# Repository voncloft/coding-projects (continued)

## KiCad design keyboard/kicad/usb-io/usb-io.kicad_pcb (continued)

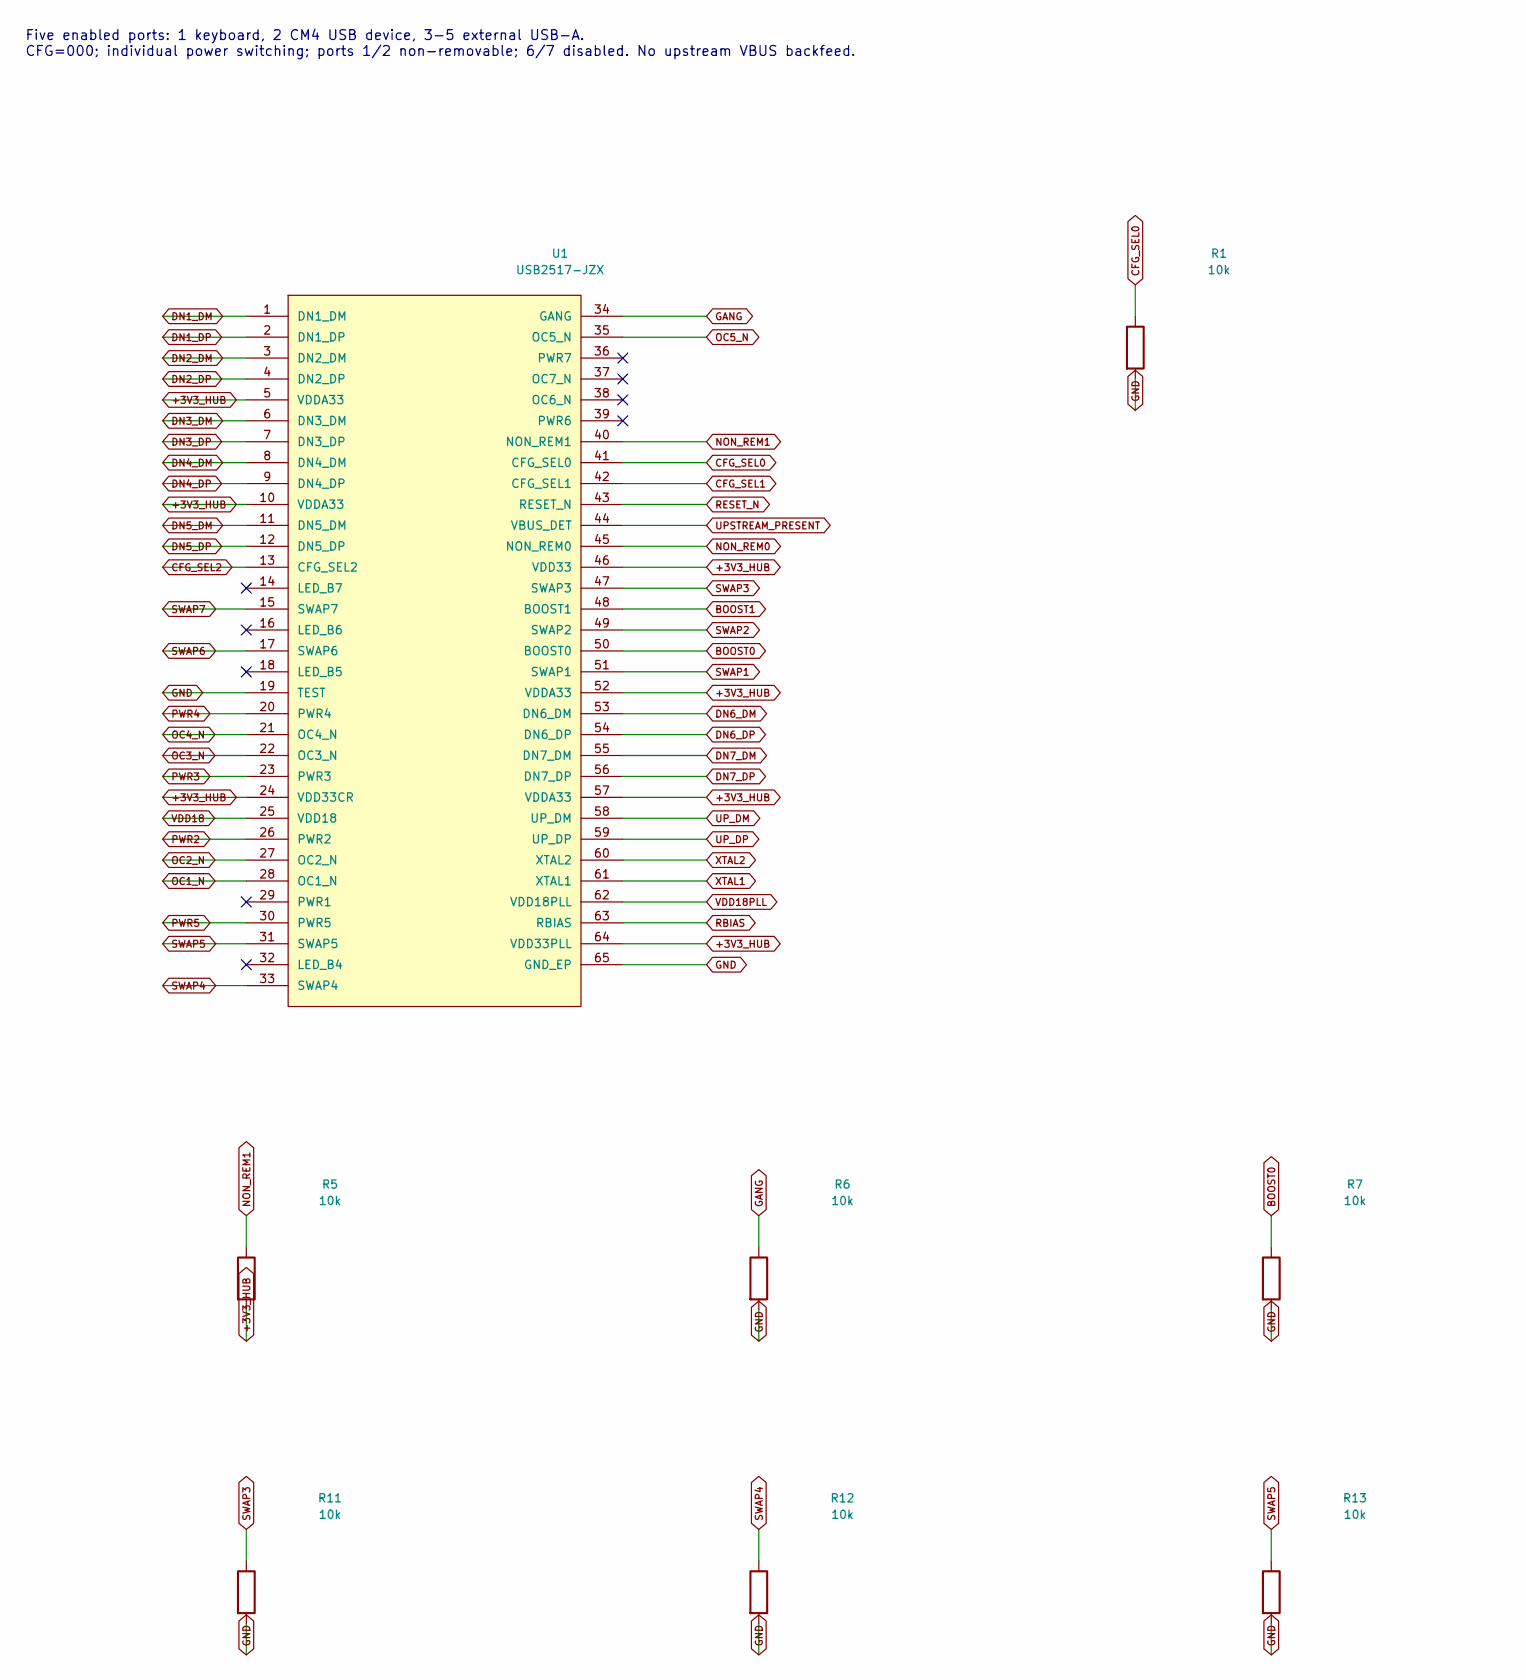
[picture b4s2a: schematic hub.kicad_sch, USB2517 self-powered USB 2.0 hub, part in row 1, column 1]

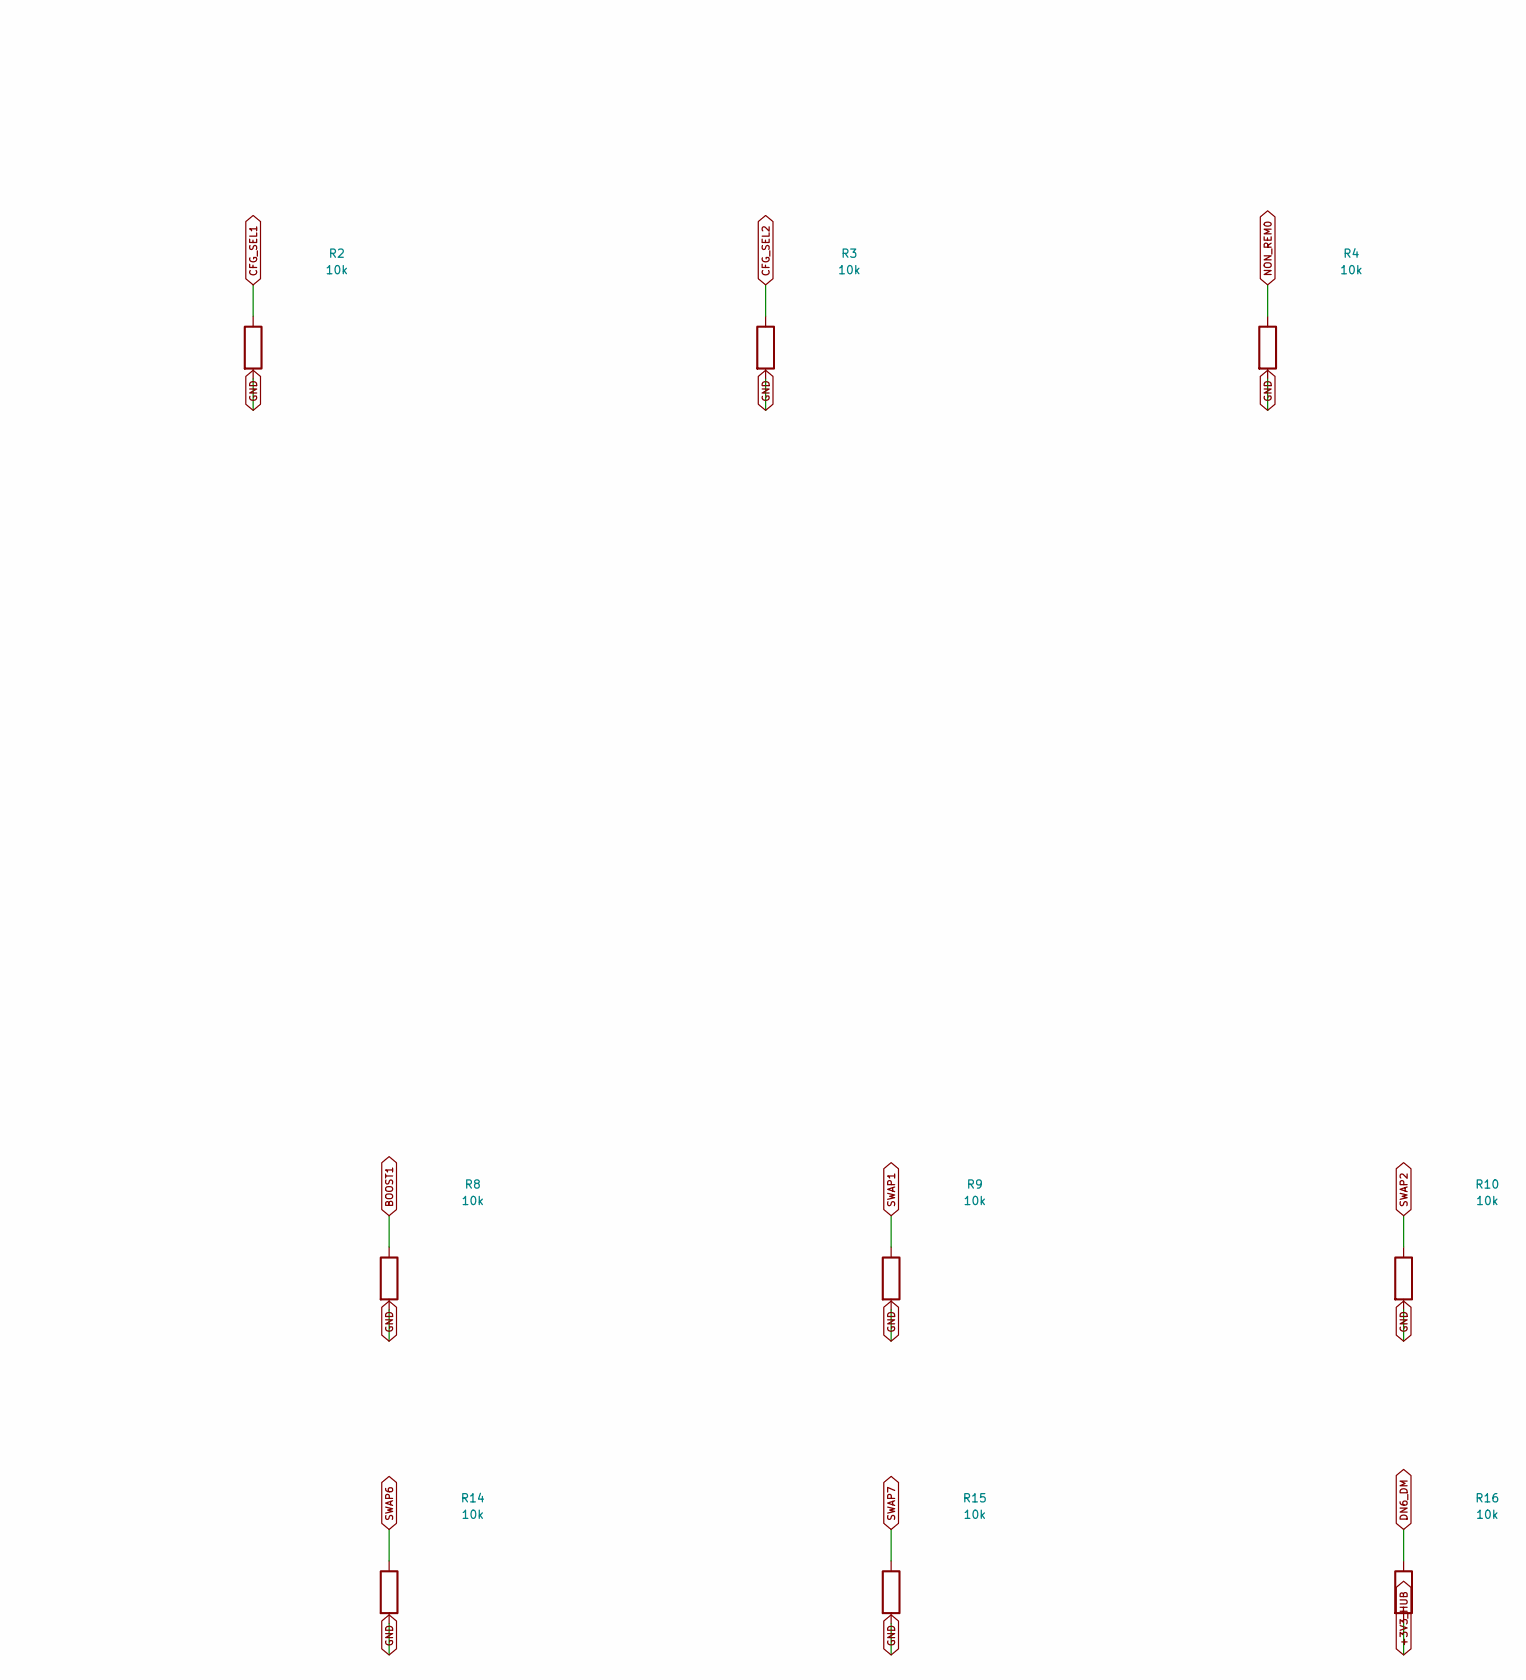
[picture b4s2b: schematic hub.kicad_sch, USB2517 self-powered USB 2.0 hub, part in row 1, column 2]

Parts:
R1, R2, R3, R4, R5, R6, R7, R8, R9, R10, R11, R12, R13, R14, R15, R16: 10k; R_0603_1608Metric
U1: USB2517-JZX; QFN-64-1EP_9x9mm_P0.5mm_EP4.7x4.7mm; MPN USB2517-JZX; JLCPCB C1521556

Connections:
+3V3_HUB: R5.2, R16.2, U1.5 (VDDA33), U1.10 (VDDA33), U1.24 (VDD33CR), U1.46 (VDD33), U1.52 (VDDA33), U1.57 (VDDA33), U1.64 (VDD33PLL); also elsewhere on the board
BOOST0: R7.1, U1.50 (BOOST0)
BOOST1: R8.1, U1.48 (BOOST1)
CFG_SEL0: R1.1, U1.41 (CFG_SEL0)
CFG_SEL1: R2.1, U1.42 (CFG_SEL1)
CFG_SEL2: R3.1, U1.13 (CFG_SEL2)
DN1_DM: U1.1 (DN1_DM); also elsewhere on the board
DN1_DP: U1.2 (DN1_DP); also elsewhere on the board
DN2_DM: U1.3 (DN2_DM); also elsewhere on the board
DN2_DP: U1.4 (DN2_DP); also elsewhere on the board
DN3_DM: U1.6 (DN3_DM); also elsewhere on the board
DN3_DP: U1.7 (DN3_DP); also elsewhere on the board
DN4_DM: U1.8 (DN4_DM); also elsewhere on the board
DN4_DP: U1.9 (DN4_DP); also elsewhere on the board
DN5_DM: U1.11 (DN5_DM); also elsewhere on the board
DN5_DP: U1.12 (DN5_DP); also elsewhere on the board
DN6_DM: R16.1, U1.53 (DN6_DM)
DN6_DP: U1.54 (DN6_DP); also elsewhere on the board
DN7_DM: U1.55 (DN7_DM); also elsewhere on the board
DN7_DP: U1.56 (DN7_DP); also elsewhere on the board
GANG: R6.1, U1.34 (GANG)
GND: R1.2, R2.2, R3.2, R4.2, R6.2, R7.2, R8.2, R9.2, R10.2, R11.2, R12.2, R13.2, R14.2, R15.2, U1.19 (TEST), U1.65 (GND_EP); also elsewhere on the board
NON_REM0: R4.1, U1.45 (NON_REM0)
NON_REM1: R5.1, U1.40 (NON_REM1)
OC1_N: U1.28 (OC1_N); also elsewhere on the board
OC2_N: U1.27 (OC2_N); also elsewhere on the board
OC3_N: U1.22 (OC3_N); also elsewhere on the board
OC4_N: U1.21 (OC4_N); also elsewhere on the board
OC5_N: U1.35 (OC5_N); also elsewhere on the board
PWR2: U1.26 (PWR2); also elsewhere on the board
PWR3: U1.23 (PWR3); also elsewhere on the board
PWR4: U1.20 (PWR4); also elsewhere on the board
PWR5: U1.30 (PWR5); also elsewhere on the board
RBIAS: U1.63 (RBIAS); also elsewhere on the board
RESET_N: U1.43 (RESET_N); also elsewhere on the board
SWAP1: R9.1, U1.51 (SWAP1)
SWAP2: R10.1, U1.49 (SWAP2)
SWAP3: R11.1, U1.47 (SWAP3)
SWAP4: R12.1, U1.33 (SWAP4)
SWAP5: R13.1, U1.31 (SWAP5)
SWAP6: R14.1, U1.17 (SWAP6)
SWAP7: R15.1, U1.15 (SWAP7)
UPSTREAM_PRESENT: U1.44 (VBUS_DET); also elsewhere on the board
UP_DM: U1.58 (UP_DM); also elsewhere on the board
UP_DP: U1.59 (UP_DP); also elsewhere on the board
VDD18: U1.25 (VDD18); also elsewhere on the board
VDD18PLL: U1.62 (VDD18PLL); also elsewhere on the board
XTAL1: U1.61 (XTAL1); also elsewhere on the board
XTAL2: U1.60 (XTAL2); also elsewhere on the board

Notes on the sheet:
Five enabled ports: 1 keyboard, 2 CM4 USB device, 3-5 external USB-A. CFG=000; individual power switching; ports 1/2 non-removable; 6/7 disabled. No upstream VBUS backfeed.

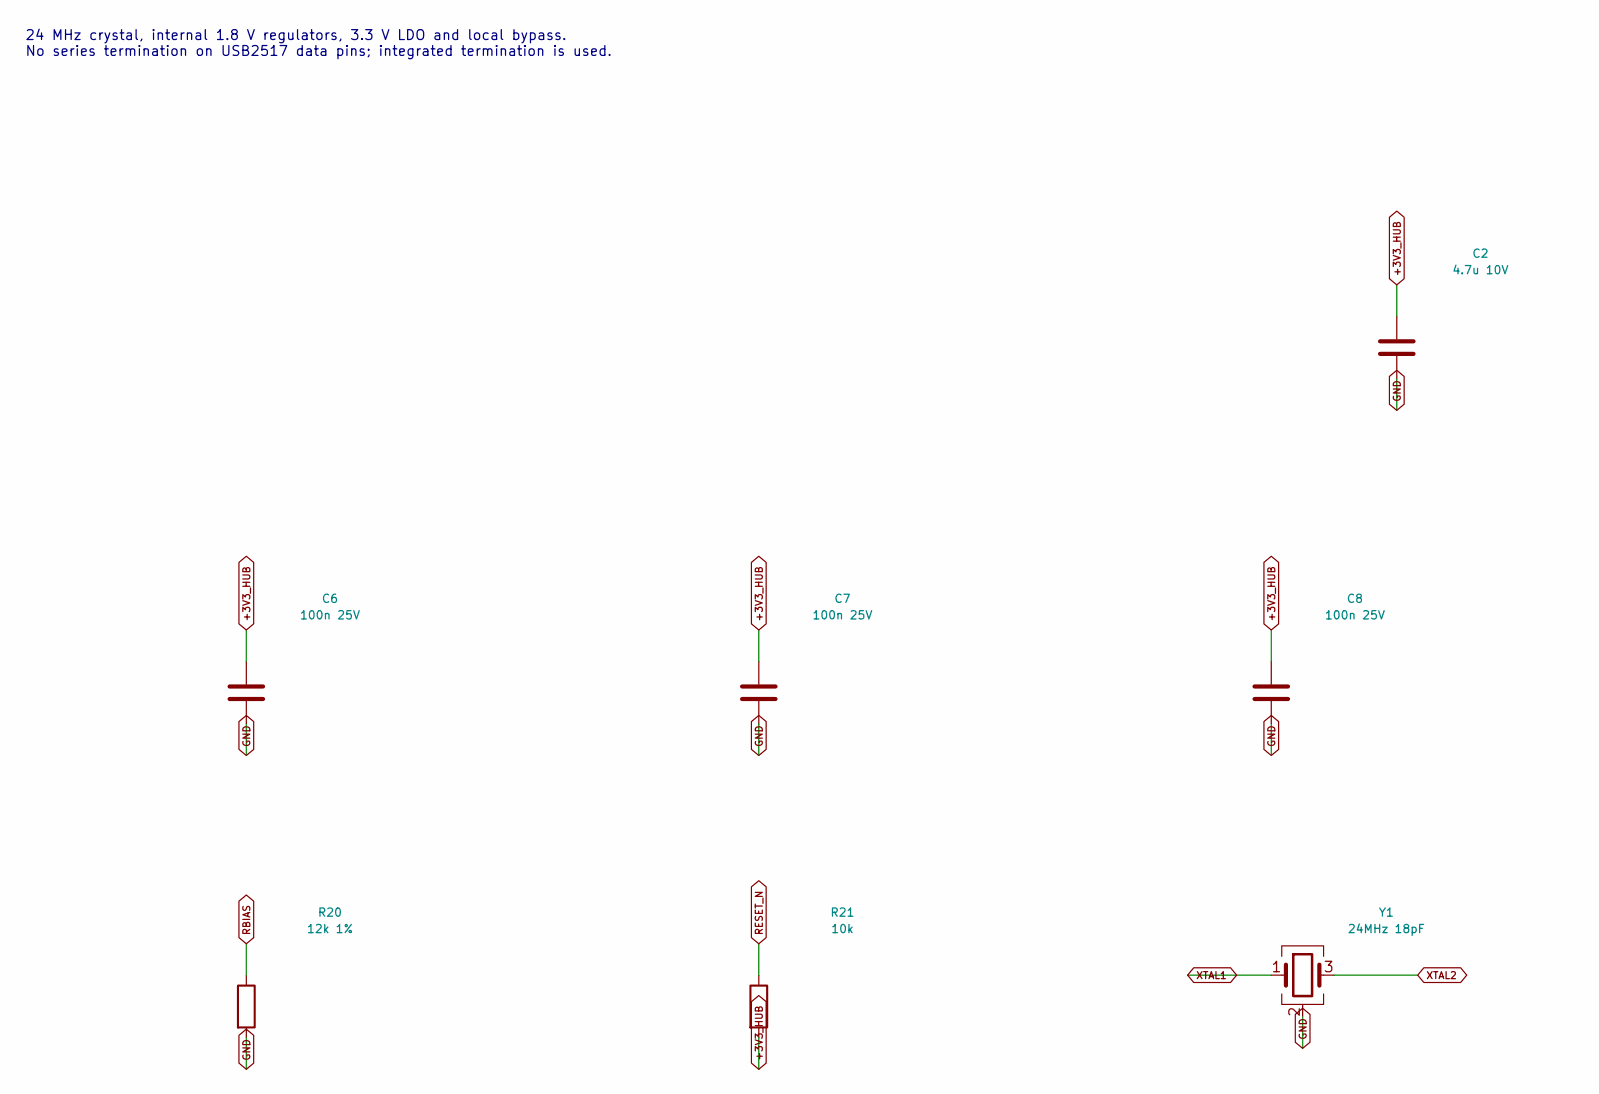
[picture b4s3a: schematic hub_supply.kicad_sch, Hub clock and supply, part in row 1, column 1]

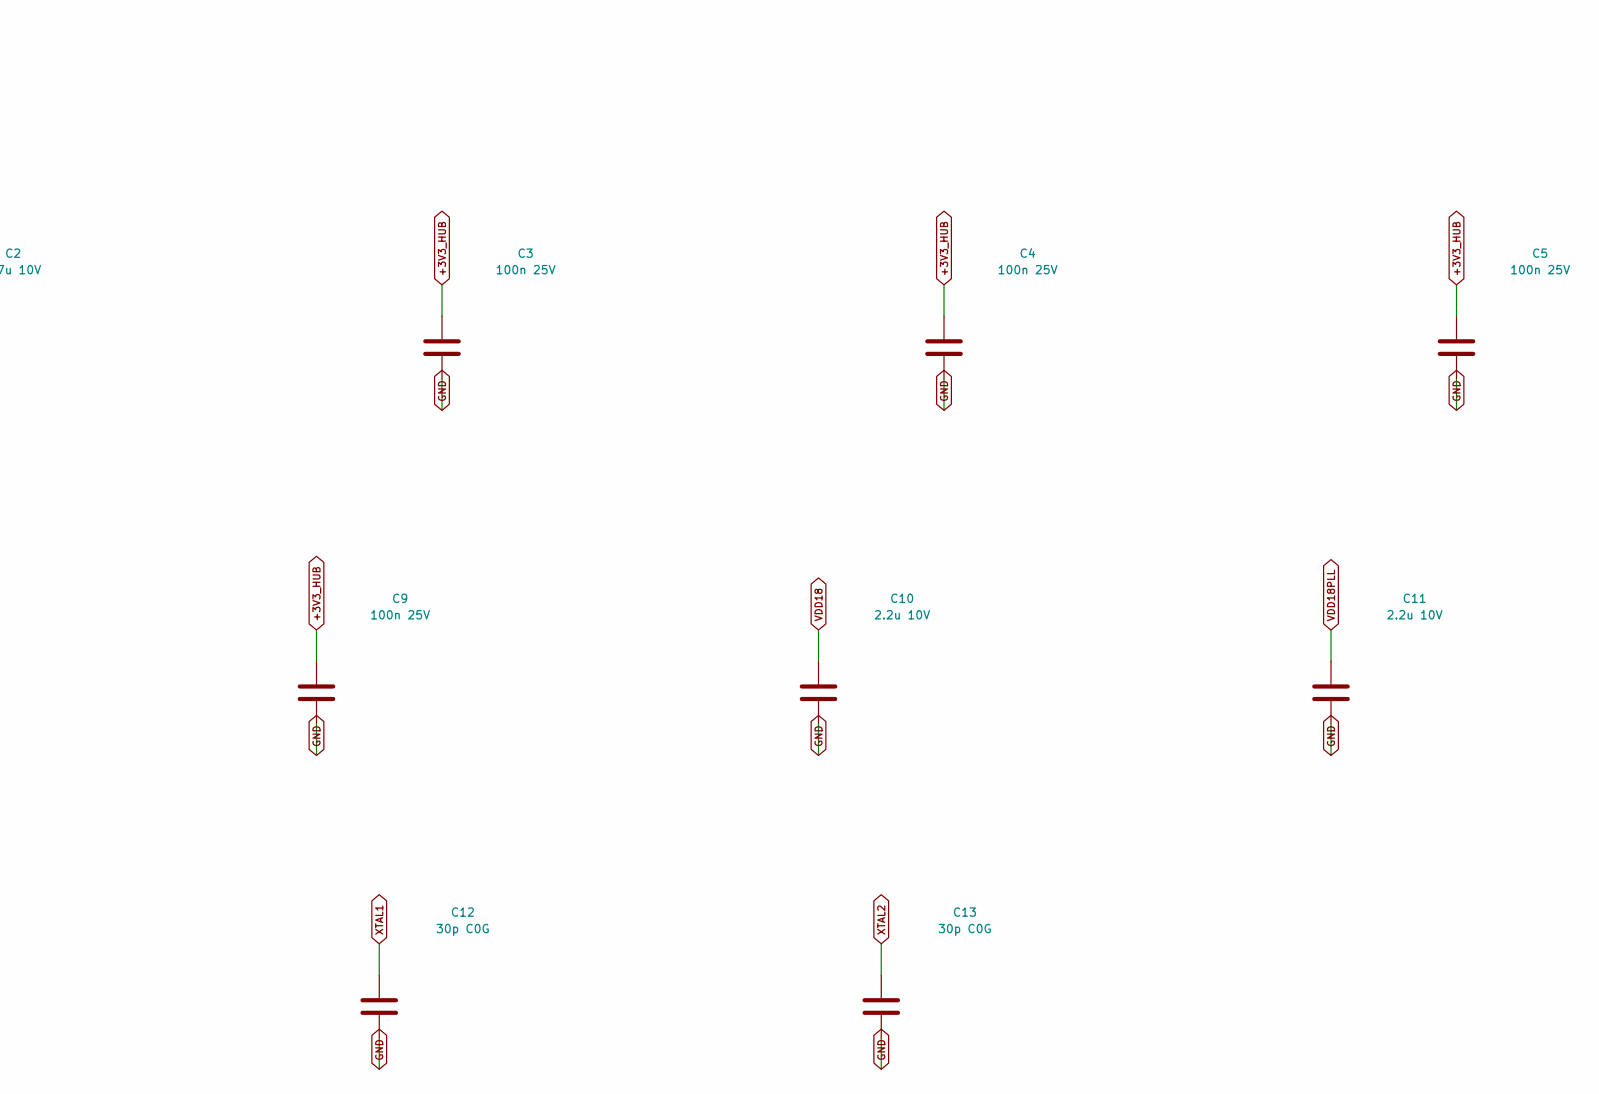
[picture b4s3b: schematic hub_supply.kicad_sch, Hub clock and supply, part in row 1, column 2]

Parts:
C2: 4.7u 10V; C_0603_1608Metric
C3, C4, C5, C6, C7, C8, C9: 100n 25V; C_0402_1005Metric
C10, C11: 2.2u 10V; C_0603_1608Metric
C12, C13: 30p C0G; C_0603_1608Metric
R20: 12k 1%; R_0603_1608Metric
R21: 10k; R_0603_1608Metric
Y1: 24MHz 18pF; Crystal_SMD_3225-4Pin_3.2x2.5mm; MPN ABM8-24.000MHZ-18-D2Y-T

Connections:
+3V3_HUB: C2.1, C3.1, C4.1, C5.1, C6.1, C7.1, C8.1, C9.1, R21.2; also elsewhere on the board
GND: C2.2, C3.2, C4.2, C5.2, C6.2, C7.2, C8.2, C9.2, C10.2, C11.2, C12.2, C13.2, R20.2, Y1.2 (G), Y1.4 (G); also elsewhere on the board
RBIAS: R20.1; also elsewhere on the board
RESET_N: R21.1; also elsewhere on the board
VDD18: C10.1; also elsewhere on the board
VDD18PLL: C11.1; also elsewhere on the board
XTAL1: C12.1, Y1.1; also elsewhere on the board
XTAL2: C13.1, Y1.3; also elsewhere on the board

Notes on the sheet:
24 MHz crystal, internal 1.8 V regulators, 3.3 V LDO and local bypass. No series termination on USB2517 data pins; integrated termination is used.

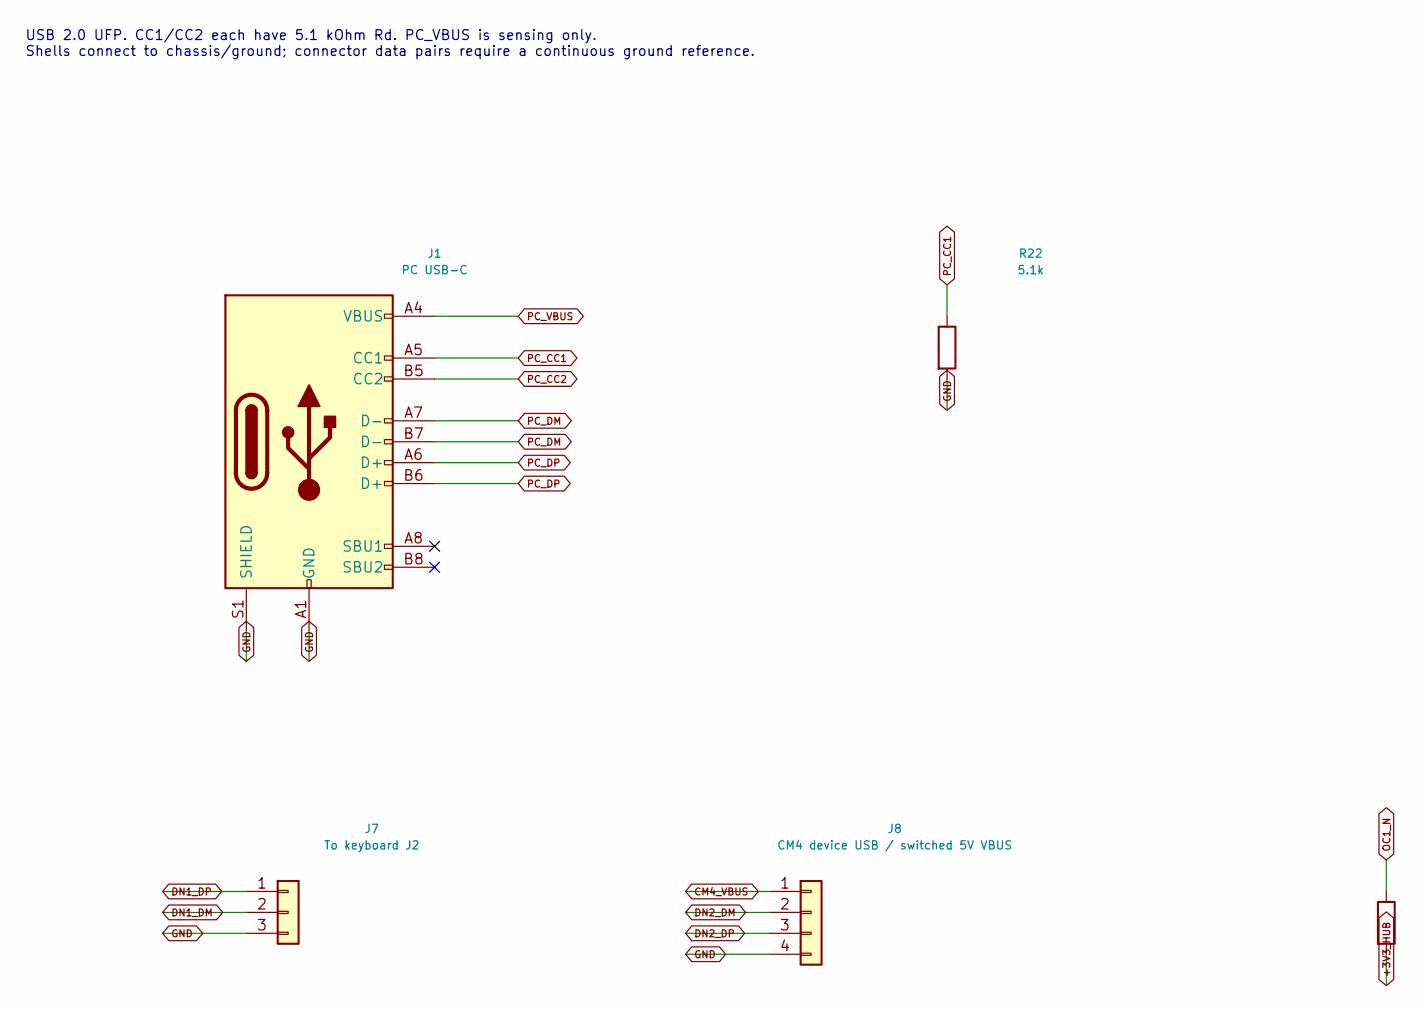
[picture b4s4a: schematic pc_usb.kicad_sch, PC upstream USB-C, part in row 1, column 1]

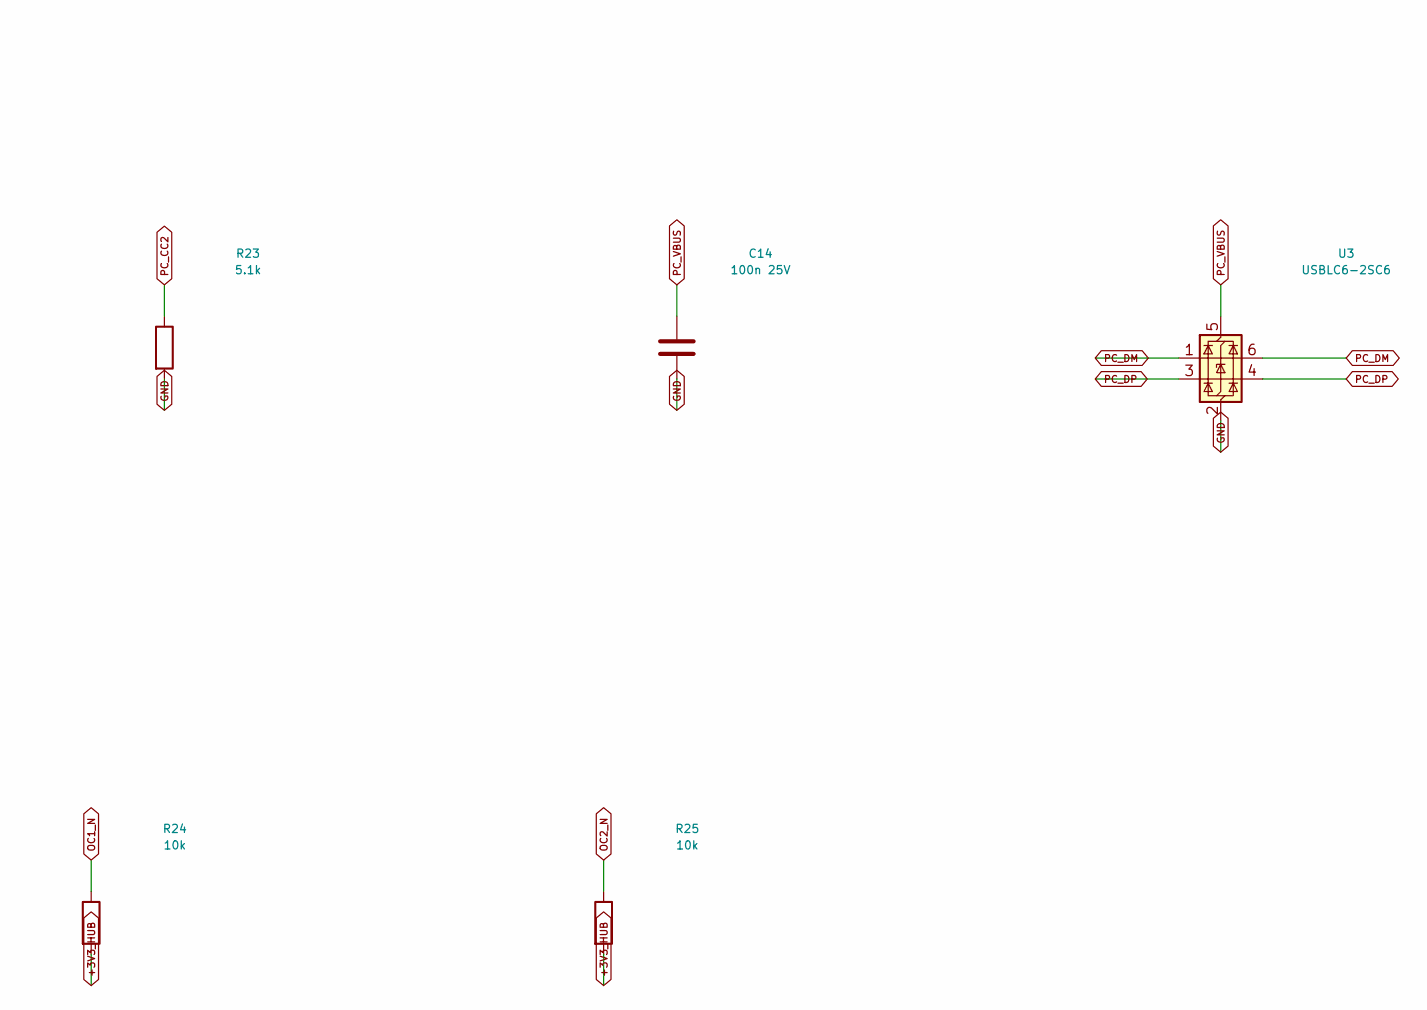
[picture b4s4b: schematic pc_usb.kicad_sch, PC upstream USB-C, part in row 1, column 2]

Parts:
C14: 100n 25V; C_0603_1608Metric
J1: PC USB-C; USB_C_Receptacle_GCT_USB4105-xx-A_16P_TopMnt_Horizontal; MPN USB4105-GF-A-060; JLCPCB C3025063
J7: To keyboard J2; JST_GH_BM03B-GHS-TBT_1x03-1MP_P1.25mm_Vertical
J8: CM4 device USB / switched 5V VBUS; JST_GH_BM04B-GHS-TBT_1x04-1MP_P1.25mm_Vertical
R22, R23: 5.1k; R_0603_1608Metric
R24, R25: 10k; R_0603_1608Metric
U3: USBLC6-2SC6; SOT-23-6; MPN USBLC6-2SC6; JLCPCB C7519

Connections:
+3V3_HUB: R24.2, R25.2; also elsewhere on the board
CM4_VBUS: J8.1; also elsewhere on the board
DN1_DM: J7.2; also elsewhere on the board
DN1_DP: J7.1; also elsewhere on the board
DN2_DM: J8.2; also elsewhere on the board
DN2_DP: J8.3; also elsewhere on the board
GND: C14.2, J1.A1 (GND), J1.A12 (GND), J1.B1 (GND), J1.B12 (GND), J1.S1 (SHIELD), J7.3, J8.4, R22.2, R23.2, U3.2 (GND); also elsewhere on the board
OC1_N: R24.1; also elsewhere on the board
OC2_N: R25.1; also elsewhere on the board
PC_CC1: J1.A5 (CC1), R22.1
PC_CC2: J1.B5 (CC2), R23.1
PC_DM: J1.A7 (D-), J1.B7 (D-), U3.1 (I/O1), U3.6 (I/O1); also elsewhere on the board
PC_DP: J1.A6 (D+), J1.B6 (D+), U3.3 (I/O2), U3.4 (I/O2); also elsewhere on the board
PC_VBUS: C14.1, J1.A4 (VBUS), J1.A9 (VBUS), J1.B4 (VBUS), J1.B9 (VBUS), U3.5 (VBUS); also elsewhere on the board

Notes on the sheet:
USB 2.0 UFP. CC1/CC2 each have 5.1 kOhm Rd. PC_VBUS is sensing only. Shells connect to chassis/ground; connector data pairs require a continuous ground reference.

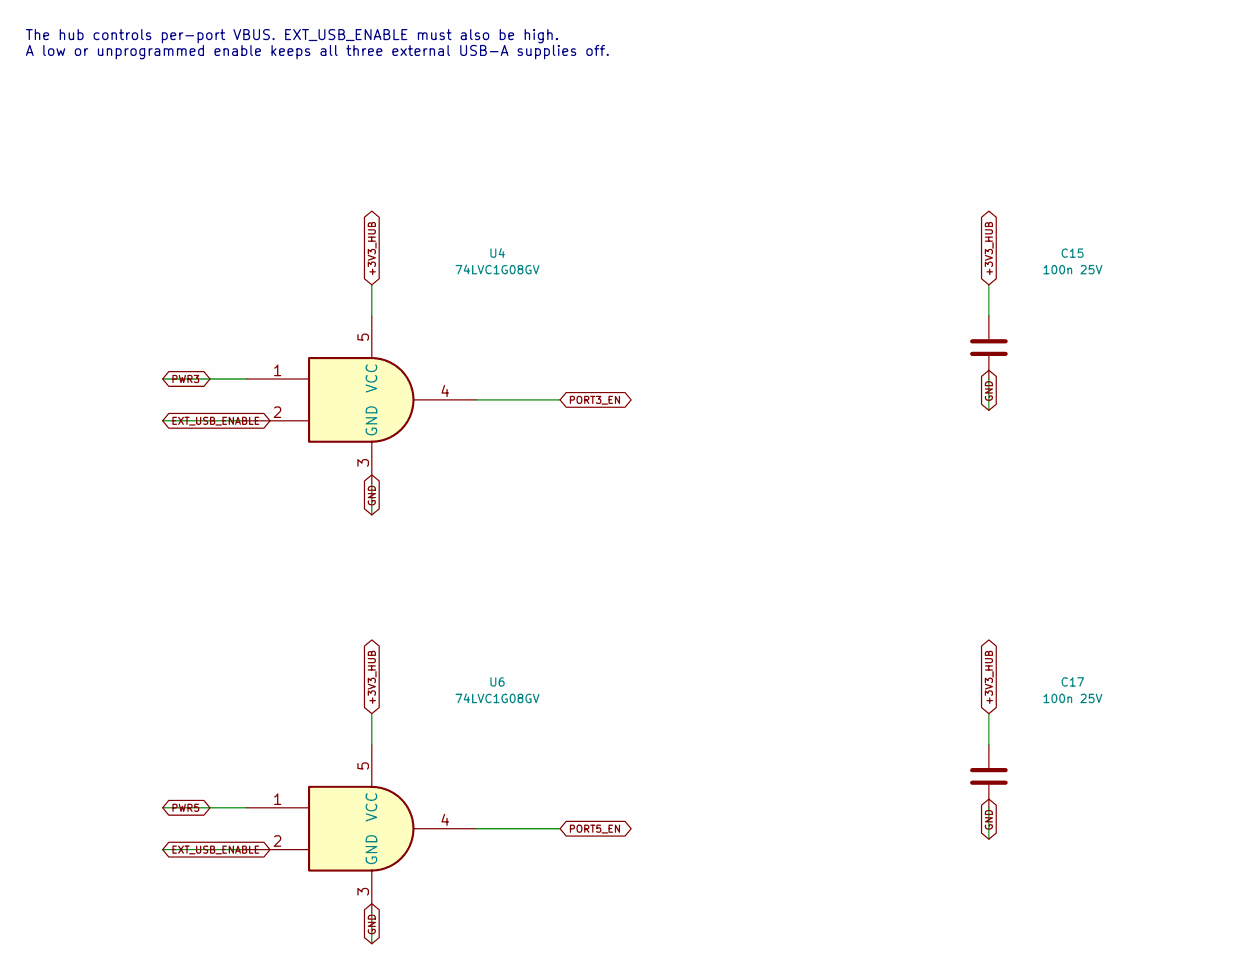
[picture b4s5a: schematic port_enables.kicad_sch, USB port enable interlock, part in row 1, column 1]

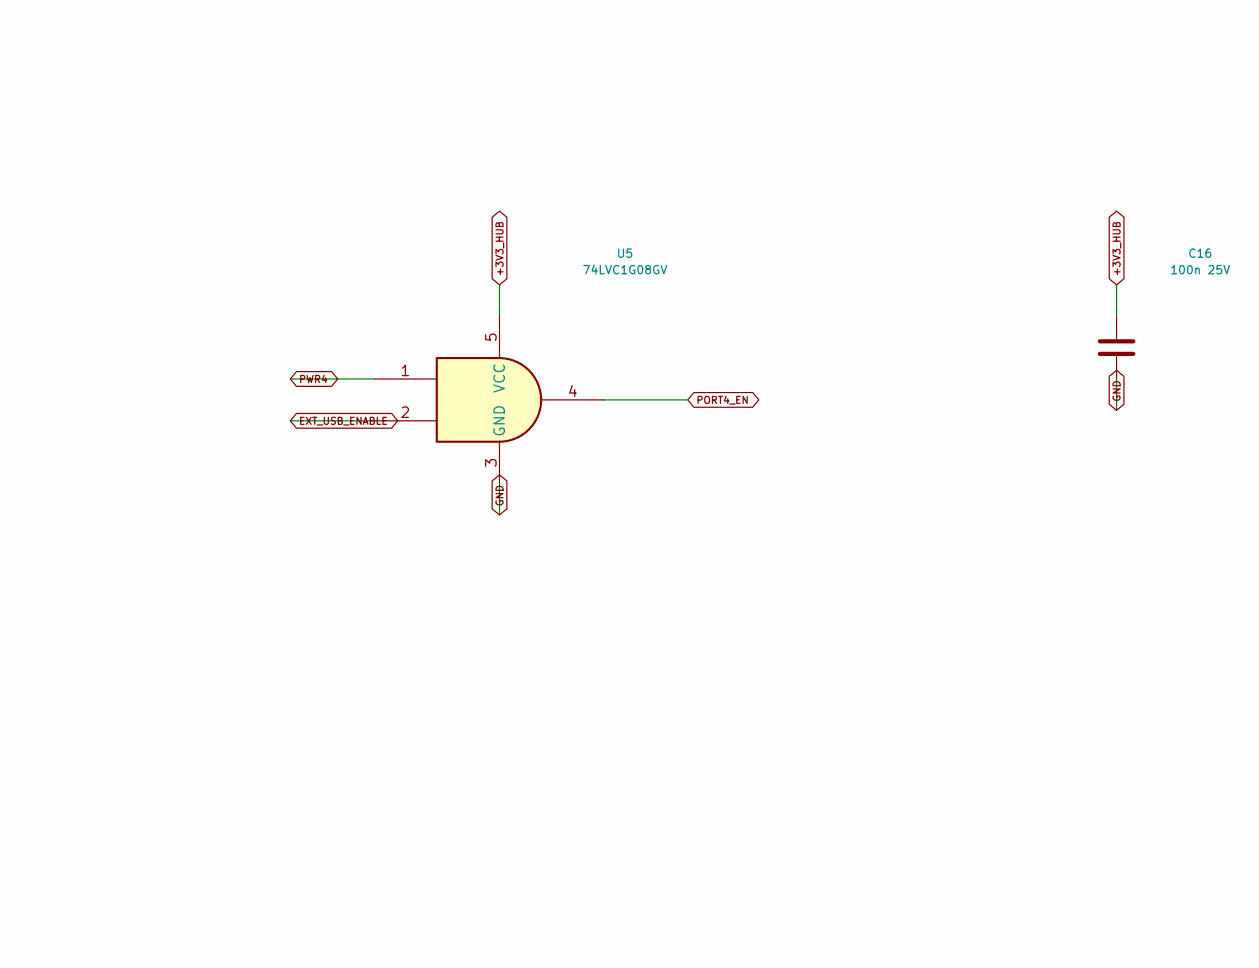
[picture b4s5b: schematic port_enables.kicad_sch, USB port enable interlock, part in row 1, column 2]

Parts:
C15, C16, C17: 100n 25V; C_0603_1608Metric
U4, U5, U6: 74LVC1G08GV; SOT-23-5; MPN 74LVC1G08GV,125

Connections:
+3V3_HUB: C15.1, C16.1, C17.1, U4.5 (VCC), U5.5 (VCC), U6.5 (VCC); also elsewhere on the board
EXT_USB_ENABLE: U4.2, U5.2, U6.2; also elsewhere on the board
GND: C15.2, C16.2, C17.2, U4.3 (GND), U5.3 (GND), U6.3 (GND); also elsewhere on the board
PORT3_EN: U4.4; also elsewhere on the board
PORT4_EN: U5.4; also elsewhere on the board
PORT5_EN: U6.4; also elsewhere on the board
PWR3: U4.1; also elsewhere on the board
PWR4: U5.1; also elsewhere on the board
PWR5: U6.1; also elsewhere on the board

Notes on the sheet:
The hub controls per-port VBUS. EXT_USB_ENABLE must also be high. A low or unprogrammed enable keeps all three external USB-A supplies off.

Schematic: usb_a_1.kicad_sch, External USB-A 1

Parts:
C18: 100n 25V; C_0603_1608Metric
C19: 150u 10V low ESR; CP_Elec_6.3x5.4; MPN EEE-FK1A151P
C20: 1u 10V; C_0603_1608Metric
J2: USB-A 1; USB_A_Molex_67643_Horizontal; MPN 67643-3910
R26: 43.2k 1%; R_0603_1608Metric
R27: 100k; R_0603_1608Metric
R28: 10k; R_0603_1608Metric
U33: TPS2553DBVR; SOT-23-6; MPN TPS2553DBVR; JLCPCB C55266
U50: USBLC6-2SC6; SOT-23-6; MPN USBLC6-2SC6; JLCPCB C7519

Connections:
+3V3_HUB: R28.2; also elsewhere on the board
+5V_IO: C18.1, U33.1 (IN); also elsewhere on the board
DN3_DM: J2.2 (D-), U50.1 (I/O1), U50.6 (I/O1); also elsewhere on the board
DN3_DP: J2.3 (D+), U50.3 (I/O2), U50.4 (I/O2); also elsewhere on the board
GND: C18.2, C19.2, C20.2, J2.4 (GND), J2.5 (Shield), R26.2, R27.2, U33.2 (GND), U50.2 (GND); also elsewhere on the board
OC3_N: R28.1, U33.4 (FAULT_N); also elsewhere on the board
PORT3_EN: R27.1, U33.3 (EN); also elsewhere on the board
PORT3_VBUS: C19.1, C20.1, J2.1 (VBUS), U33.6 (OUT), U50.5 (VBUS)
PORT3_VBUS_ILIM: R26.1, U33.5 (ILIM)

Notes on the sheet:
USB 2.0 downstream port 3: 500 mA permitted load. TPS2553 overcurrent reports to hub. 150 uF minimum port reservoir; fault limits include resistor/device tolerance.

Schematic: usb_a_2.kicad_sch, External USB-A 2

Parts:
C21: 100n 25V; C_0603_1608Metric
C22: 150u 10V low ESR; CP_Elec_6.3x5.4; MPN EEE-FK1A151P
C23: 1u 10V; C_0603_1608Metric
J3: USB-A 2; USB_A_Molex_67643_Horizontal; MPN 67643-3910
R29: 43.2k 1%; R_0603_1608Metric
R30: 100k; R_0603_1608Metric
R31: 10k; R_0603_1608Metric
U34: TPS2553DBVR; SOT-23-6; MPN TPS2553DBVR; JLCPCB C55266
U51: USBLC6-2SC6; SOT-23-6; MPN USBLC6-2SC6; JLCPCB C7519

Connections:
+3V3_HUB: R31.2; also elsewhere on the board
+5V_IO: C21.1, U34.1 (IN); also elsewhere on the board
DN4_DM: J3.2 (D-), U51.1 (I/O1), U51.6 (I/O1); also elsewhere on the board
DN4_DP: J3.3 (D+), U51.3 (I/O2), U51.4 (I/O2); also elsewhere on the board
GND: C21.2, C22.2, C23.2, J3.4 (GND), J3.5 (Shield), R29.2, R30.2, U34.2 (GND), U51.2 (GND); also elsewhere on the board
OC4_N: R31.1, U34.4 (FAULT_N); also elsewhere on the board
PORT4_EN: R30.1, U34.3 (EN); also elsewhere on the board
PORT4_VBUS: C22.1, C23.1, J3.1 (VBUS), U34.6 (OUT), U51.5 (VBUS)
PORT4_VBUS_ILIM: R29.1, U34.5 (ILIM)

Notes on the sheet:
USB 2.0 downstream port 4: 500 mA permitted load. TPS2553 overcurrent reports to hub. 150 uF minimum port reservoir; fault limits include resistor/device tolerance.

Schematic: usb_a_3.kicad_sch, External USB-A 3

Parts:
C24: 100n 25V; C_0603_1608Metric
C25: 150u 10V low ESR; CP_Elec_6.3x5.4; MPN EEE-FK1A151P
C26: 1u 10V; C_0603_1608Metric
J4: USB-A 3; USB_A_Molex_67643_Horizontal; MPN 67643-3910
R32: 43.2k 1%; R_0603_1608Metric
R33: 100k; R_0603_1608Metric
R34: 10k; R_0603_1608Metric
U35: TPS2553DBVR; SOT-23-6; MPN TPS2553DBVR; JLCPCB C55266
U52: USBLC6-2SC6; SOT-23-6; MPN USBLC6-2SC6; JLCPCB C7519

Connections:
+3V3_HUB: R34.2; also elsewhere on the board
+5V_IO: C24.1, U35.1 (IN); also elsewhere on the board
DN5_DM: J4.2 (D-), U52.1 (I/O1), U52.6 (I/O1); also elsewhere on the board
DN5_DP: J4.3 (D+), U52.3 (I/O2), U52.4 (I/O2); also elsewhere on the board
GND: C24.2, C25.2, C26.2, J4.4 (GND), J4.5 (Shield), R32.2, R33.2, U35.2 (GND), U52.2 (GND); also elsewhere on the board
OC5_N: R34.1, U35.4 (FAULT_N); also elsewhere on the board
PORT5_EN: R33.1, U35.3 (EN); also elsewhere on the board
PORT5_VBUS: C25.1, C26.1, J4.1 (VBUS), U35.6 (OUT), U52.5 (VBUS)
PORT5_VBUS_ILIM: R32.1, U35.5 (ILIM)

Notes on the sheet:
USB 2.0 downstream port 5: 500 mA permitted load. TPS2553 overcurrent reports to hub. 150 uF minimum port reservoir; fault limits include resistor/device tolerance.

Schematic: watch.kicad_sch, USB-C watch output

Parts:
C27: 100n 25V; C_0603_1608Metric
C28: 10u 10V; C_0805_2012Metric
C29: 150u 10V low ESR; CP_Elec_6.3x5.4; MPN EEE-FK1A151P
J5: WATCH USB-C; USB_C_Receptacle_GCT_USB4105-xx-A_16P_TopMnt_Horizontal; MPN USB4105-GF-A-060; JLCPCB C3025063
R35: 100k 1%; R_0603_1608Metric
R36: 100k; R_0603_1608Metric
R37: 10k; R_0603_1608Metric
U20: TPS25810RVCR; QFN-20-1EP_3x4mm_P0.5mm_EP1.65x2.65mm; MPN TPS25810RVCR; JLCPCB C473913

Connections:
+3V3_AON: R37.2; also elsewhere on the board
+5V_IO: C27.1, C29.1, U20.2 (IN1), U20.3 (IN1), U20.4 (IN2), U20.5 (AUX), U20.7 (CHG); also elsewhere on the board
GND: C27.2, C28.2, C29.2, J5.A1 (GND), J5.A12 (GND), J5.B1 (GND), J5.B12 (GND), J5.S1 (SHIELD), R36.2, U20.8 (CHG_HI), U20.12 (GND), U20.21 (EP); also elsewhere on the board
WATCH_CC1: J5.A5 (CC1), U20.11 (CC1)
WATCH_CC2: J5.B5 (CC2), U20.13 (CC2)
WATCH_ENABLE: R36.1, U20.6 (EN); also elsewhere on the board
WATCH_FAULT_N: R37.1, U20.1 (FAULT_N); also elsewhere on the board
WATCH_REF: R35.1, U20.10 (REF)
WATCH_REF_RTN: R35.2, U20.9 (REF_RTN)
WATCH_VBUS: C28.1, J5.A4 (VBUS), J5.A9 (VBUS), J5.B4 (VBUS), J5.B9 (VBUS), U20.14 (OUT), U20.15 (OUT)

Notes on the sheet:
TPS25810: 5 V, 1.5 A advertised. CC attach detection, current limit, VCONN, discharge. Charge-only output for existing Samsung USB-C watch puck. Fast-charge behavior needs a hardware test.

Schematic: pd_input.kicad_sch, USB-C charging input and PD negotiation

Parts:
C30, C32: 1u 50V; C_0805_2012Metric
C31: 100n 50V; C_0603_1608Metric
D1: BZT52C12; D_SOD-123; MPN BZT52C12
J6: CHARGE / DATA / PROGRAM USB-C; USB_C_Receptacle_GCT_USB4105-xx-A_16P_TopMnt_Horizontal; MPN USB4105-GF-A-060; JLCPCB C3025063
Q1, Q2: AO4407A; SOIC-8_3.9x4.9mm_P1.27mm; MPN AO4407A; JLCPCB C16072
R38: 22.6k 1%; R_0603_1608Metric
R39: 5.1k; R_0603_1608Metric
R40: 49.9k; R_0603_1608Metric
U21: HUSB238_002DD; WDFN-10-1EP_3x3mm_P0.5mm_EP1.8x2.5mm; MPN HUSB238_002DD; JLCPCB C7471904

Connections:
CHARGE_CC1: J6.A5 (CC1), U21.4 (CC1)
CHARGE_CC2: J6.B5 (CC2), U21.5 (CC2)
CHARGE_DM: J6.A7 (D-), J6.B7 (D-); also elsewhere on the board
CHARGE_DP: J6.A6 (D+), J6.B6 (D+); also elsewhere on the board
GND: C30.2, C31.2, C32.2, J6.A1 (GND), J6.A12 (GND), J6.B1 (GND), J6.B12 (GND), J6.S1 (SHIELD), R38.2, U21.11 (GND); also elsewhere on the board
I2C_SCL: U21.7 (SCL); also elsewhere on the board
I2C_SDA: U21.6 (SDA); also elsewhere on the board
PD_GATE: D1.2 (A), Q1.4 (G), Q2.4 (G), R39.2, R40.1
PD_GATE_DRIVE: R39.1, U21.10 (GATE)
PD_IN: C31.1, C32.1, Q2.5 (D), Q2.6 (D), Q2.7 (D), Q2.8 (D); also elsewhere on the board
PD_ISET: R38.1, U21.9 (ISET)
PD_RAW: C30.1, J6.A4 (VBUS), J6.A9 (VBUS), J6.B4 (VBUS), J6.B9 (VBUS), Q1.5 (D), Q1.6 (D), Q1.7 (D), Q1.8 (D), U21.1 (VIN); also elsewhere on the board
PD_SOURCE: D1.1 (K), Q1.1 (S), Q1.2 (S), Q1.3 (S), Q2.1 (S), Q2.2 (S), Q2.3 (S), R40.2

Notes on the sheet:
HUSB238 requests up to 20 V / 3 A. BQ25798 input current stays conservative until firmware validates contract. Back-to-back PMOS isolate the input in both directions. 12 V gate clamp protects VGS.

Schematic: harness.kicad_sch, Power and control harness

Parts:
C33: 100n 25V; C_0603_1608Metric
H1, H2, H3, H4, H5: M2 clearance; MountingHole_2.2mm_M2
J9: To power J1; JST_VH_B2P-VH_1x02_P3.96mm_Vertical
J10: From power J2; JST_VH_B4P-VH_1x04_P3.96mm_Vertical
J11: To power J3; JST_GH_BM08B-GHS-TBT_1x08-1MP_P1.25mm_Vertical
R41: 100k; R_0603_1608Metric
SW1: OFF / ON; SW_SPDT_CK_JS102011SAQN; MPN JS102011SAQN

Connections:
+3V3_AON: J11.1, SW1.3 (C); also elsewhere on the board
+5V_CORE: J10.1; also elsewhere on the board
+5V_IO: J10.3; also elsewhere on the board
EXT_USB_ENABLE: J11.6; also elsewhere on the board
GND: C33.2, J9.2, J10.2, J10.4, J11.2, R41.2, SW1.1 (A); also elsewhere on the board
I2C_SCL: J11.4; also elsewhere on the board
I2C_SDA: J11.3; also elsewhere on the board
PD_IN: J9.1; also elsewhere on the board
POWER_REQUEST: C33.1, J11.5, R41.1, SW1.2 (B)
WATCH_ENABLE: J11.7; also elsewhere on the board
WATCH_FAULT_N: J11.8; also elsewhere on the board

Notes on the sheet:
Rear switch is a logic request. Firmware completes Linux shutdown before releasing MAIN_ENABLE. J9/J10 use separate keyed power harnesses; signals use a separate GH harness. No raw battery here.

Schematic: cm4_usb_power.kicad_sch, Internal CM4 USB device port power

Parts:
C34: 100n 25V; C_0603_1608Metric
C35: 1u 10V; C_0603_1608Metric
C36: 150u 10V low ESR; CP_Elec_6.3x5.4; MPN EEE-FK1A151P
R42: 43.2k 1%; R_0603_1608Metric
R43: 100k; R_0603_1608Metric
R44: 10k; R_0603_1608Metric
U36: TPS2553DBVR; SOT-23-6; MPN TPS2553DBVR; JLCPCB C55266

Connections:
+3V3_HUB: R44.2; also elsewhere on the board
+5V_CORE: C34.1, U36.1 (IN); also elsewhere on the board
CM4_VBUS: C35.1, C36.1, U36.6 (OUT); also elsewhere on the board
CM4_VBUS_ILIM: R42.1, U36.5 (ILIM)
GND: C34.2, C35.2, C36.2, R42.2, R43.2, U36.2 (GND); also elsewhere on the board
OC2_N: R44.1, U36.4 (FAULT_N); also elsewhere on the board
PWR2: R43.1, U36.3 (EN); also elsewhere on the board

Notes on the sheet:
Switched 5 V VBUS follows hub port 2. CM4 is self-powered from its core rail. The carrier must sense this VBUS through a suitable divider; never connect 5 V directly to GPIO.

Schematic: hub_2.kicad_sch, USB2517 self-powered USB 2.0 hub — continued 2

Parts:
R17, R18, R19: 10k; R_0603_1608Metric

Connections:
+3V3_HUB: R17.2, R18.2, R19.2; also elsewhere on the board
DN6_DP: R17.1; also elsewhere on the board
DN7_DM: R18.1; also elsewhere on the board
DN7_DP: R19.1; also elsewhere on the board

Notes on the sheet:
Five enabled ports: 1 keyboard, 2 CM4 USB device, 3-5 external USB-A. CFG=000; individual power switching; ports 1/2 non-removable; 6/7 disabled. No upstream VBUS backfeed.
